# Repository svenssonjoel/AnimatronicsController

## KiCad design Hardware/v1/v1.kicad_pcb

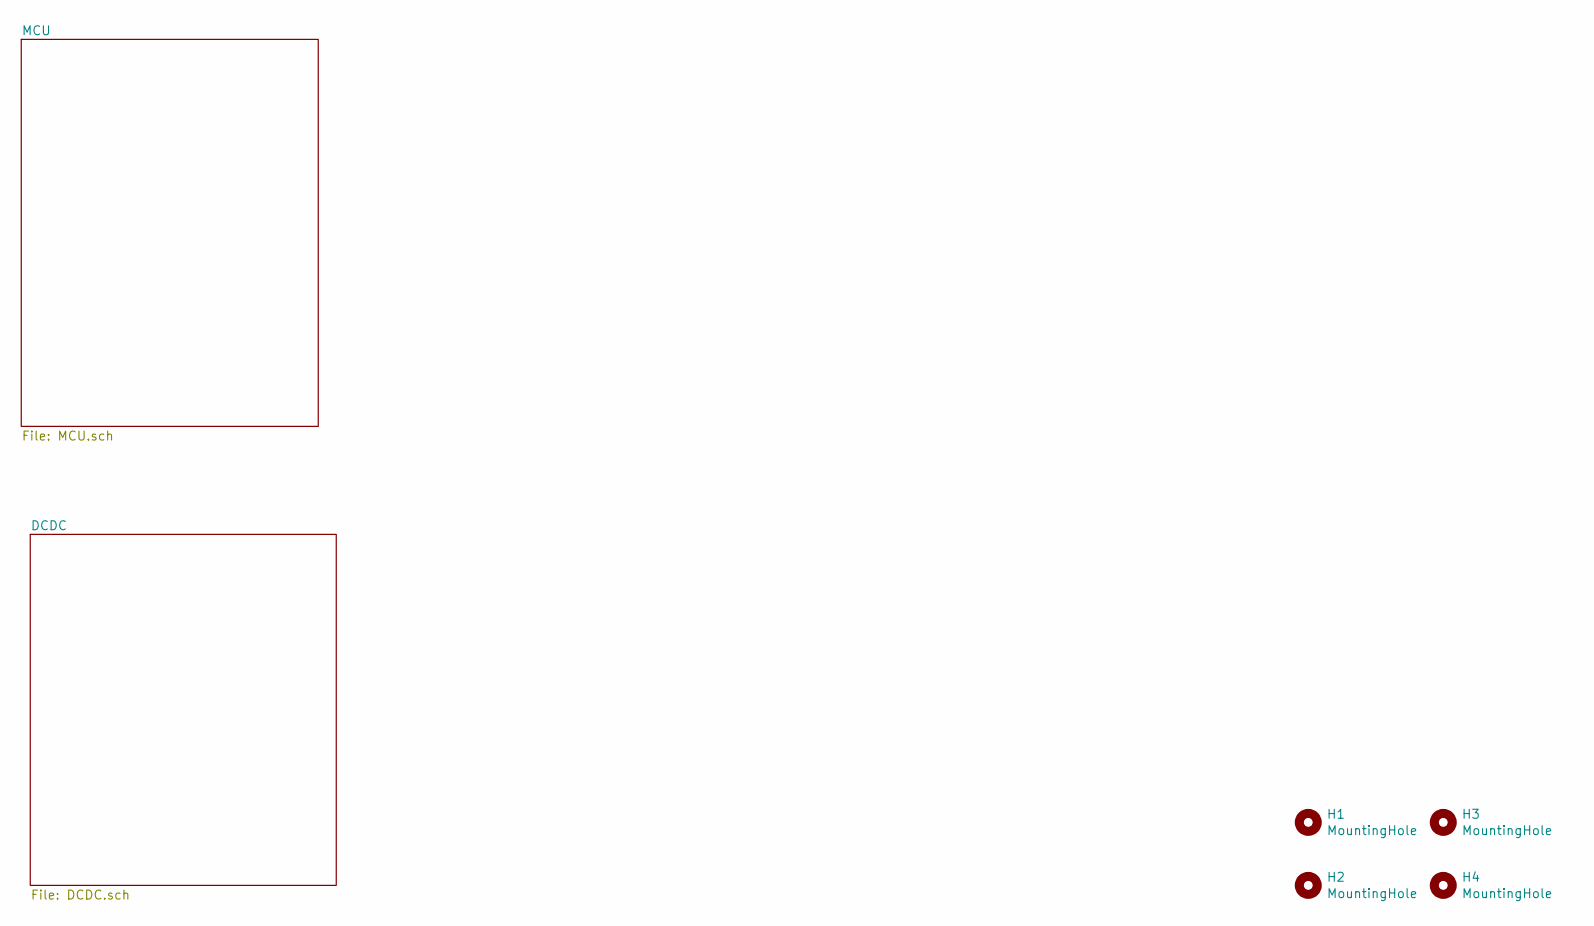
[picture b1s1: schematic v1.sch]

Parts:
H1, H2, H3, H4: MountingHole; MountingHole_3.2mm_M3

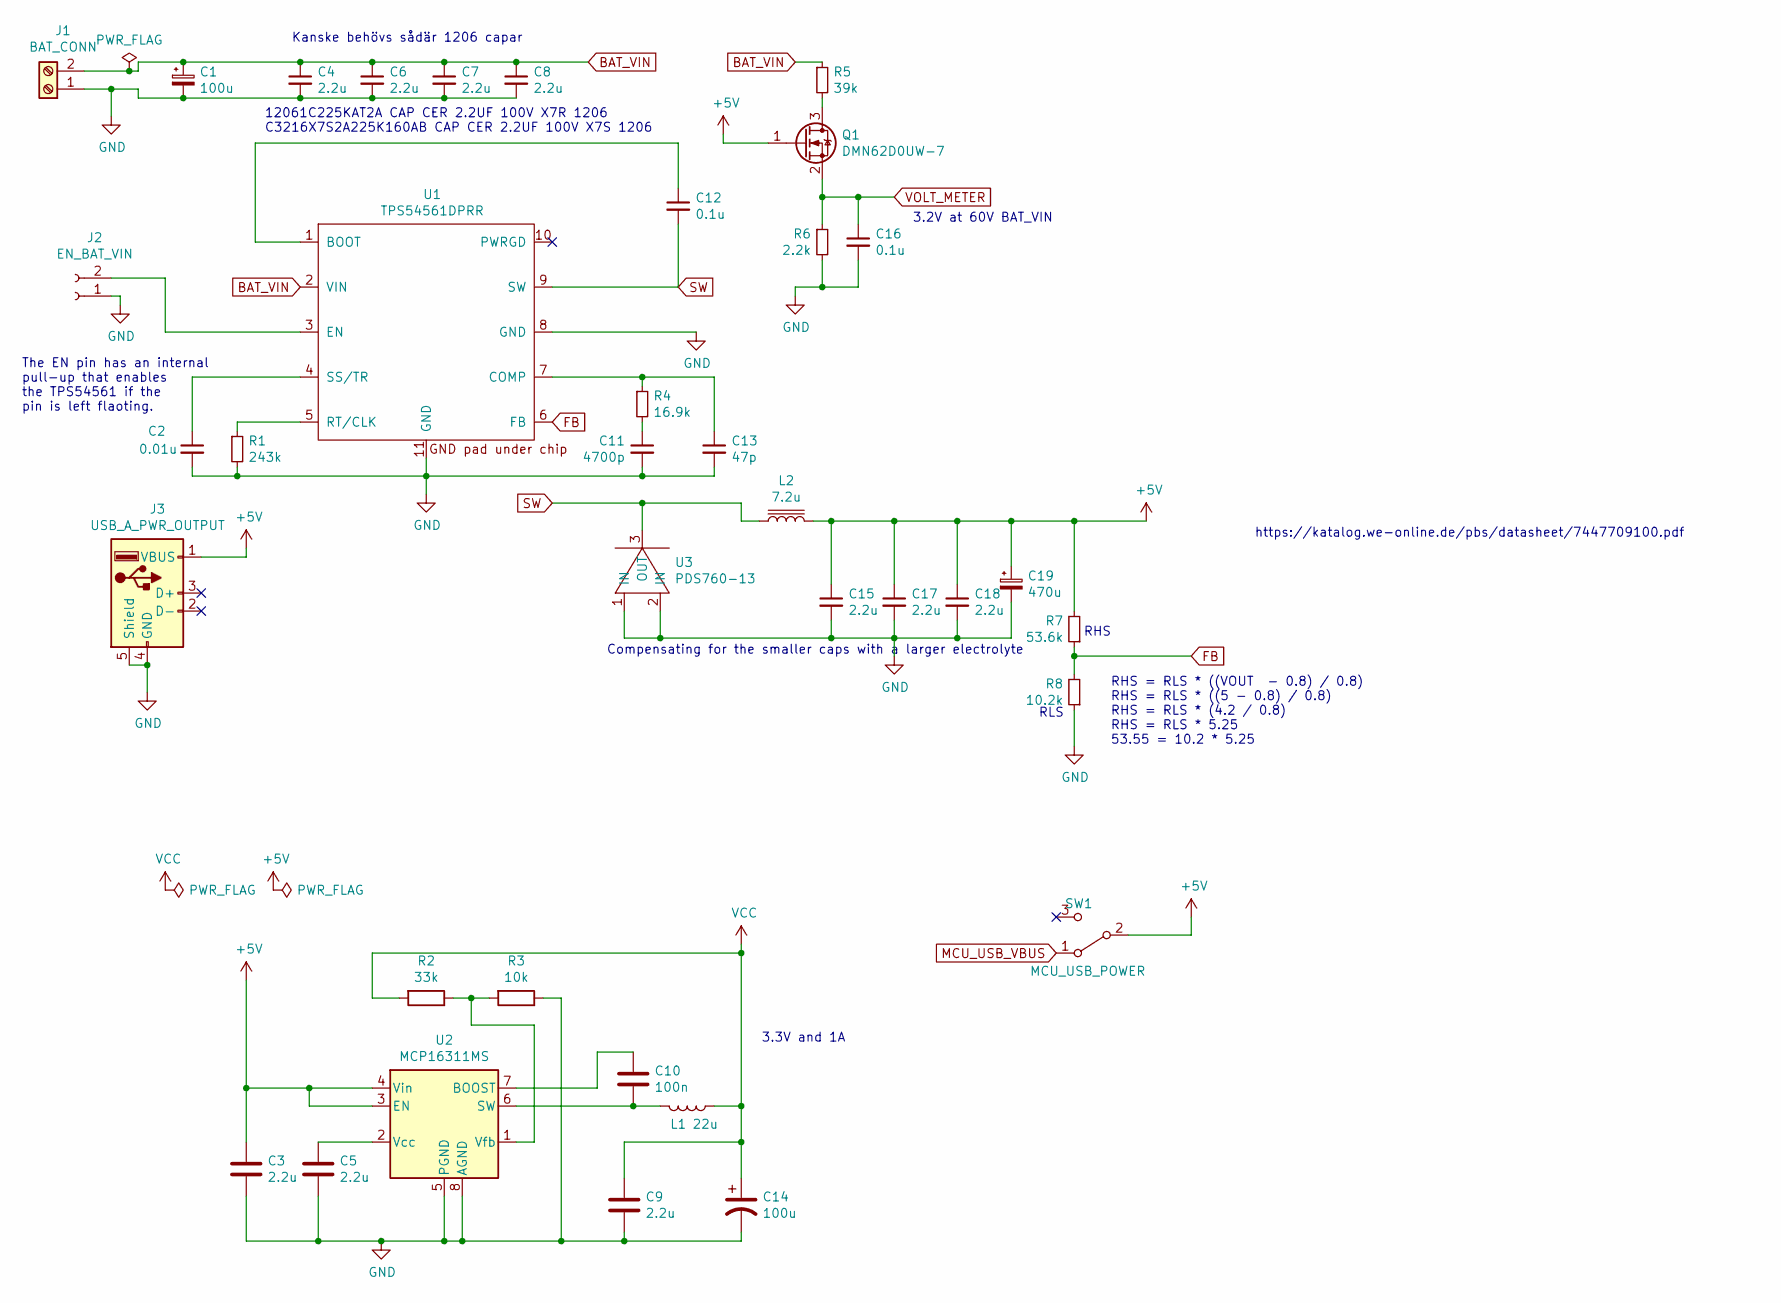
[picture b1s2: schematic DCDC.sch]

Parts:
C1: 100u; CP_Radial_D10.0mm_P5.00mm
C2: 0.01u; C_0603_1608Metric
C3, C5, C9, C15, C17, C18: 2.2u; C_0603_1608Metric
C4, C6, C7, C8: 2.2u; C_1206_3216Metric
C10: 100n; C_0603_1608Metric
C11: 4700p; C_0603_1608Metric
C12, C16: 0.1u; C_0603_1608Metric
C13: 47p; C_0603_1608Metric
C14: 100u; CP_EIA-3528-12_Kemet-T
C19: 470u; CP_Radial_D10.0mm_P5.00mm
J1: BAT_CONN; TerminalBlock_Phoenix_PT-1,5-2-5.0-H_1x02_P5.00mm_Horizontal
J2: EN_BAT_VIN; JST_PH_B2B-PH-K_1x02_P2.00mm_Vertical
J3: USB_A_PWR_OUTPUT; USB_A_Stewart_SS-52100-001_Horizontal
L1: 22u; L_Taiyo-Yuden_MD-5050
L2: 7.2u; L_12x12mm_H8mm
Q1: DMN62D0UW-7; SOT-323_SC-70
R1: 243k; R_0603_1608Metric
R2: 33k; R_0603_1608Metric
R3: 10k; R_0603_1608Metric
R4: 16.9k; R_0603_1608Metric
R5: 39k; R_0603_1608Metric
R6: 2.2k; R_0603_1608Metric
R7: 53.6k; R_0603_1608Metric
R8: 10.2k; R_0603_1608Metric
SW1: MCU_USB_POWER; SW_SPDT_PCM12
U1: TPS54561DPRR; TI-DPR; digikey 296-40803-1-ND
U2: MCP16311MS; MSOP-8_3x3mm_P0.65mm
U3: PDS760-13; POWERDI5

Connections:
+5V: C3.1, C15.1, C17.1, C18.1, C19.1, J3.1 (VBUS), L2.2, Q1.1 (G), R7.2, SW1.2 (B), U2.3 (EN), U2.4 (Vin); also elsewhere on the board
BAT_VIN: C1.1, C4.1, C6.1, C7.1, C8.1, J1.2, R5.1, U1.2 (VIN)
FB: R7.1, R8.2, U1.6 (FB)
GND: C1.2, C2.2, C3.2, C4.2, C5.2, C6.2, C7.2, C8.2, C9.2, C11.2, C13.2, C14.2, C15.2, C16.2, C17.2, C18.2, C19.2, J1.1, J2.1, J3.4 (GND), J3.5 (Shield), R1.2, R3.1, R6.2, R8.1, U1.8 (GND), U1.11 (GND), U2.5 (PGND), U2.8 (AGND), U3.1 (IN), U3.2 (IN); also elsewhere on the board
MCU_USB_VBUS: SW1.1 (A); also elsewhere on the board
unnamed: C2.1, U1.4 (SS/TR)
unnamed: C5.1, U2.2 (Vcc)
unnamed: C10.1, U2.7 (BOOST)
unnamed: C10.2, L1.2, U2.6 (SW)
unnamed: C11.1, R4.2
unnamed: C12.1, U1.1 (BOOT)
unnamed: C13.1, R4.1, U1.7 (COMP)
unnamed: J2.2, U1.3 (EN)
unnamed: Q1.3 (D), R5.2
unnamed: R1.1, U1.5 (RT/CLK)
unnamed: R2.1, R3.2, U2.1 (Vfb)
SW: C12.2, L2.1, U1.9 (SW), U3.3 (OUT)
VCC: C9.1, C14.1, L1.1, R2.2; also elsewhere on the board
VOLT_METER: C16.1, Q1.2 (S), R6.1; also elsewhere on the board

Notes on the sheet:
3.3V and 1A
The EN pin has an internal pull-up that enables the TPS54561 if the pin is left flaoting.
Kanske behövs sådär 1206 capar
https://katalog.we-online.de/pbs/datasheet/7447709100.pdf
3.2V at 60V BAT_VIN
12061C225KAT2A CAP CER 2.2UF 100V X7R 1206 C3216X7S2A225K160AB CAP CER 2.2UF 100V X7S 1206
RHS = RLS * ((VOUT - 0.8) / 0.8) RHS = RLS * ((5 - 0.8) / 0.8) RHS = RLS * (4.2 / 0.8) RHS = RLS * 5.25 53.55 = 10.2 * 5.25
RHS
RLS
Compensating for the smaller caps with a larger electrolyte

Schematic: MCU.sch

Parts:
C20, C23: 15p; C_0603_1608Metric
C21, C22, C24, C25, C27, C28, C29, C30, C31, C32, C33, C34: 2.2u; C_0603_1608Metric
C26: 100n; C_0603_1608Metric
D1: RED; LED_0603_1608Metric
D2: GREEN; LED_0603_1608Metric
J4: GPIO1; JST_PH_B4B-PH-K_1x04_P2.00mm_Vertical
J5: GPIO2; JST_PH_B4B-PH-K_1x04_P2.00mm_Vertical
J6: GPIO3; JST_PH_B4B-PH-K_1x04_P2.00mm_Vertical
J10: DACS; JST_PH_B2B-PH-K_1x02_P2.00mm_Vertical
J11: SERV_0; PinHeader_1x03_P2.54mm_Vertical
J12: SERV_1; PinHeader_1x03_P2.54mm_Vertical
J13: SERV_2; PinHeader_1x03_P2.54mm_Vertical
J14: SERV_3; PinHeader_1x03_P2.54mm_Vertical
J15: SERV_4; PinHeader_1x03_P2.54mm_Vertical
J16: SERV_5; PinHeader_1x03_P2.54mm_Vertical
J17: SERV_6; PinHeader_1x03_P2.54mm_Vertical
J18: SERV_7; PinHeader_1x03_P2.54mm_Vertical
J19: CAN; JST_PH_B4B-PH-K_1x04_P2.00mm_Vertical
J20: USB_B_Mini; USB_Mini-B_Lumberg_2486_01_Horizontal
P1: SWD; JST_PH_B6B-PH-K_1x06_P2.00mm_Vertical
R9, R10, R22, R27: 1k; R_0603_1608Metric
R11, R14, R15, R16, R17, R18, R19, R20, R21: 220R; R_0603_1608Metric
R12, R13: 22R; R_0603_1608Metric
SW2: BOOT0; SW_SPDT_PCM12
U4: BMI160; Bosch_LGA-14_3x2.5mm_P0.5mm; digikey 828-1057-1-ND
U5: STM32F405RGTx; LQFP-64_10x10mm_P0.5mm
U6: TJA1051TK-3; DFN-8-1EP_3x3mm_P0.65mm_EP1.55x2.4mm
Y1: 8Mhz; Crystal_SMD_5032-4Pin_5.0x3.2mm

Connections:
+5V: C28.2, J11.2, J12.2, J13.2, J14.2, J15.2, J16.2, J17.2, J18.2, J19.4, U6.3 (VCC); also elsewhere on the board
/MCU/GP1: J4.2, U5.9 (PC1)
/MCU/GP2: J4.3, U5.10 (PC2)
/MCU/GP3: J4.4, U5.11 (PC3)
/MCU/GP4: J5.2, U5.53 (PC12)
/MCU/GP5: J5.3, U5.2 (PC13)
/MCU/GP6: J5.4, U5.3 (PC14)
/MCU/GP7: J6.2, U5.22 (PA6)
/MCU/GP8: J6.3, U5.23 (PA7)
/MCU/GP9: J6.4, U5.41 (PA8)
/MCU/SERV1: R14.2, U5.14 (PA0)
/MCU/SERV2: R15.2, U5.15 (PA1)
/MCU/SERV3: R16.2, U5.16 (PA2)
/MCU/SERV4: R17.2, U5.17 (PA3)
/MCU/SERV5: R18.2, U5.26 (PB0)
/MCU/SERV6: R19.2, U5.27 (PB1)
/MCU/SERV7: R20.2, U5.55 (PB3)
/MCU/SERV8: R21.2, U5.56 (PB4)
CANH: J19.3, R11.1, U6.7 (CANH)
CANL: J19.2, R11.2, U6.6 (CANL)
CAN_RX: U5.61 (PB8), U6.4 (RXD)
CAN_TX: U5.62 (PB9), U6.1 (TXD)
GND: C20.1, C21.2, C22.2, C23.1, C24.2, C25.2, C26.1, C27.2, C28.1, C29.2, C30.2, C31.2, C32.2, C33.2, C34.2, D1.1 (K), D2.1 (K), J4.1, J5.1, J6.1, J11.3, J12.3, J13.3, J14.3, J15.3, J16.3, J17.3, J18.3, J19.1, J20.5, J20.6, P1.4, SW2.1 (A), U4.1 (SDO), U4.6 (GNDIO), U4.7 (GND), U5.12 (VSSA), U5.18 (VSS), U5.28 (PB2), U5.63 (VSS), U6.2 (GND), U6.8 (S), U6.9 (GND), Y1.2, Y1.4; also elsewhere on the board
IMU_INT2: U4.9 (INT2), U5.25 (PC5)
LED0: R22.2, U5.51 (PC10)
LED1: R27.2, U5.52 (PC11)
MCU_USB_DM: J20.2, R12.1
MCU_USB_DP: J20.3, R13.1
MCU_USB_VBUS: J20.1, U5.42 (PA9); also elsewhere on the board
NRST: C26.2, P1.2, U5.7 (NRST)
unnamed: C20.2, U5.6 (PH1), Y1.3
unnamed: C23.2, U5.5 (PH0), Y1.1
unnamed: C24.1, U5.31 (VCAP_1)
unnamed: C25.1, U5.47 (VCAP_2)
unnamed: D1.2 (A), R22.1
unnamed: D2.2 (A), R27.1
unnamed: J10.1, U5.20 (PA4)
unnamed: J10.2, U5.21 (PA5)
unnamed: J11.1, R14.1
unnamed: J12.1, R15.1
unnamed: J13.1, R16.1
unnamed: J14.1, R17.1
unnamed: J15.1, R18.1
unnamed: J16.1, R19.1
unnamed: J17.1, R20.1
unnamed: J18.1, R21.1
unnamed: R12.2, U5.44 (PA11)
unnamed: R13.2, U5.45 (PA12)
unnamed: SW2.2 (B), U5.60 (BOOT0)
SCL: R10.2, U4.13 (SCx), U5.29 (PB10)
SDA: R9.2, U4.14 (SDx), U5.30 (PB11)
SWCLK: P1.5, U5.49 (PA14)
SWDIO: P1.3, U5.46 (PA13)
VCC: C21.1, C22.1, C27.1, C29.1, C30.1, C31.1, C32.1, C33.1, C34.1, P1.6, R9.1, R10.1, SW2.3 (C), U4.5 (VDDIO), U4.8 (VDD), U4.12 (CSB), U5.1 (VBAT), U5.13 (VDDA), U5.19 (VDD), U5.32 (VDD), U5.48 (VDD), U5.64 (VDD), U6.5 (VIO); also elsewhere on the board
VOLT_METER: U5.8 (PC0); also elsewhere on the board

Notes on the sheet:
place close to pin 1, 19, 32, 48, 64, 13
PC0 - PC5 has ADC
Servo connectors
LQFP64 TIM 2,3,4,5 PWM (TIM1 is more capable than TIM2 - 5 TIM1 CH1 PIN 23 (N), 27(N), 34(N), 36(N), 41 TIM1 CH2 PIN 42 TIM1 CH3 PIN 43 TIM1 CH4 PIN 44 (Maybe prefer these ?) TIM2 CH1 PIN 14, 21 TIM2 CH2 PIN 15, 55 TIM2 CH3 PIN 16, 29 TIM2 CH4 PIN 17, 30 TIM3 CH1 PIN 37, 56 TIM3 CH2 PIN 38 TIM3 CH3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
Dubbelkoll CSB - VCC. vi ska ha I2c
Place near VDD/GND BMI160

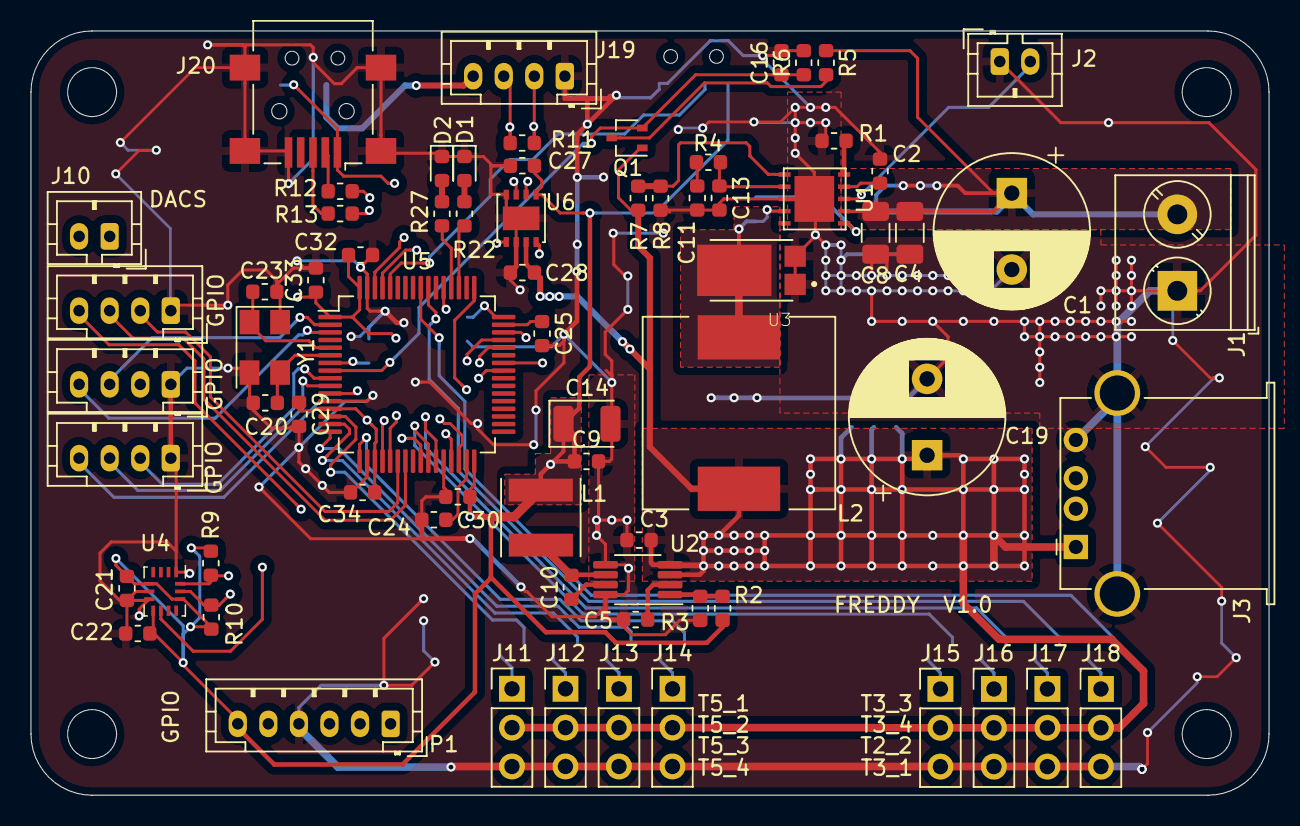
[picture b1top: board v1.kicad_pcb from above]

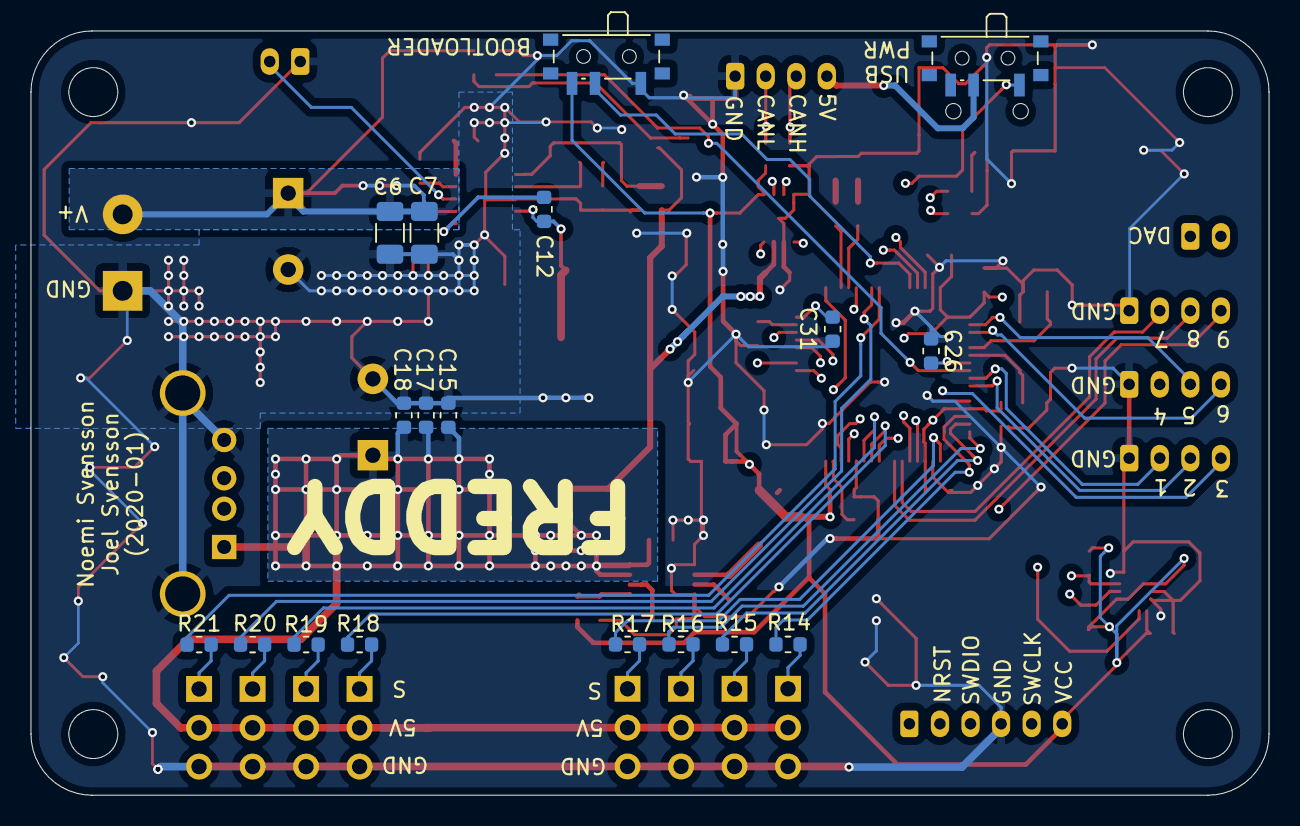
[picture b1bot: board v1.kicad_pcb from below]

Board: 4 copper layers, 81.0 x 50.0 mm, 93 parts (18 on the bottom side), 69 nets.

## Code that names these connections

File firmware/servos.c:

/*
    Copyright 2020 Joel Svensson	svenssonjoel@yahoo.se

    This program is free software: you can redistribute it and/or modify
    it under the terms of the GNU General Public License as published by
    the Free Software Foundation, either version 3 of the License, or
    (at your option) any later version.

    This program is distributed in the hope that it will be useful,
    but WITHOUT ANY WARRANTY; without even the implied warranty of
    MERCHANTABILITY or FITNESS FOR A PARTICULAR PURPOSE.  See the
    GNU General Public License for more details.

    You should have received a copy of the GNU General Public License
    along with this program.  If not, see <http://www.gnu.org/licenses/>.
*/

#include <stdint.h>
#include "servos.h"

#include "hal.h"
#include "hal_pwm.h"
#include "hal_pal.h"

/* 
   Alternate function mappings for 
   PA0 - PA3 to use tim 5 
   PB0 - PB1 to use tim 3
   PB3       to use tim 2
    ---- PB4       to use tim 3 --- should not have used this!
*/ 
#define GPIO_AF_TIM5   ((uint8_t)0x02)
#define GPIO_AF_TIM3   ((uint8_t)0x02)  
#define GPIO_AF_TIM2   ((uint8_t)0x01)

/* pwmconfig to use for TIM5.
   Here all channels are used. 
*/ 
static PWMConfig pwmcfg_tim5 = {
  1000000,
  20000,
  NULL,
  {
    {PWM_OUTPUT_ACTIVE_HIGH, NULL},
    {PWM_OUTPUT_ACTIVE_HIGH, NULL},
    {PWM_OUTPUT_ACTIVE_HIGH, NULL},
    {PWM_OUTPUT_ACTIVE_HIGH, NULL}
  },
  0,
  0
};

static PWMConfig pwmcfg_tim3 = {
  1000000,
  20000,
  NULL,
  {
    {PWM_OUTPUT_ACTIVE_HIGH, NULL},
    {PWM_OUTPUT_DISABLED,    NULL},
    {PWM_OUTPUT_ACTIVE_HIGH, NULL},
    {PWM_OUTPUT_ACTIVE_HIGH, NULL}
  },
  0,
  0,
};

/*
static PWMConfig pwmcfg_tim2 = {
  1000000,
  20000,
  NULL,
  {
    {PWM_OUTPUT_DISABLED,    NULL},
    {PWM_OUTPUT_ACTIVE_HIGH, NULL},
    {PWM_OUTPUT_DISABLED,    NULL},
    {PWM_OUTPUT_DISABLED,    NULL},
  },
  0,
  0,
};
*/

void servos_init(void) {

  palSetPadMode(GPIOA, 0,
		PAL_MODE_ALTERNATE(GPIO_AF_TIM5) |
		PAL_STM32_OSPEED_HIGHEST |
		PAL_STM32_PUPDR_FLOATING);
  palSetPadMode(GPIOA, 1,
		PAL_MODE_ALTERNATE(GPIO_AF_TIM5) |
		PAL_STM32_OSPEED_HIGHEST |
		PAL_STM32_PUPDR_FLOATING);
  palSetPadMode(GPIOA, 2,
		PAL_MODE_ALTERNATE(GPIO_AF_TIM5) |
		PAL_STM32_OSPEED_HIGHEST |
		PAL_STM32_PUPDR_FLOATING);
  palSetPadMode(GPIOA, 3,
		PAL_MODE_ALTERNATE(GPIO_AF_TIM5) |
		PAL_STM32_OSPEED_HIGHEST |
		PAL_STM32_PUPDR_FLOATING);

  palSetPadMode(GPIOB, 0,
		PAL_MODE_ALTERNATE(GPIO_AF_TIM3) |
	        PAL_STM32_OSPEED_HIGHEST |
		PAL_STM32_PUPDR_FLOATING);
  palSetPadMode(GPIOB, 1,
		PAL_MODE_ALTERNATE(GPIO_AF_TIM3) |
		PAL_STM32_OSPEED_HIGHEST |
		PAL_STM32_PUPDR_FLOATING);
  palSetPadMode(GPIOB, 4,
		PAL_MODE_ALTERNATE(GPIO_AF_TIM3) |
		PAL_STM32_OSPEED_HIGHEST |
		PAL_STM32_PUPDR_FLOATING);

  //palSetPadMode(GPIOB, 3,
  //		PAL_MODE_ALTERNATE(GPIO_AF_TIM2) |
  //		PAL_STM32_OSPEED_HIGHEST |
  //		PAL_STM32_PUPDR_FLOATING);

  
  //pwmStart(&PWMD2, &pwmcfg_tim2);
  pwmStart(&PWMD3, &pwmcfg_tim3);
  pwmStart(&PWMD5, &pwmcfg_tim5);

  //pwmEnableChannel(&PWMD2, 1, 0); /* Second channel of tim 2 */

  pwmEnableChannel(&PWMD5, 0, 0);
  pwmEnableChannel(&PWMD5, 1, 0);
  pwmEnableChannel(&PWMD5, 2, 0);
  pwmEnableChannel(&PWMD5, 3, 0);
  
  pwmEnableChannel(&PWMD3, 0, 0);
  pwmEnableChannel(&PWMD3, 2, 0);
  pwmEnableChannel(&PWMD3, 3, 0);
}
  

extern void servos_set_duty(uint8_t servos, unsigned int duty) {

  if (servos & SERVO1) {
    pwmEnableChannel(&PWMD5, 0, PWM_PERCENTAGE_TO_WIDTH(&PWMD5, duty));
  }

  if (servos & SERVO2) {
    pwmEnableChannel(&PWMD5, 1, PWM_PERCENTAGE_TO_WIDTH(&PWMD5, duty));
  }

  if (servos & SERVO3) {
    pwmEnableChannel(&PWMD5, 2, PWM_PERCENTAGE_TO_WIDTH(&PWMD5, duty));
  }

  if (servos & SERVO4) {
    pwmEnableChannel(&PWMD5, 3, PWM_PERCENTAGE_TO_WIDTH(&PWMD5, duty));
  }

  if (servos & SERVO5) { 
    pwmEnableChannel(&PWMD3, 0, PWM_PERCENTAGE_TO_WIDTH(&PWMD3, duty));
  }

  if (servos & SERVO6) {
    pwmEnableChannel(&PWMD3, 2, PWM_PERCENTAGE_TO_WIDTH(&PWMD3, duty));
  }

  if (servos & SERVO7) {
    //pwmEnableChannel(&PWMD2, 1, PWM_PERCENTAGE_TO_WIDTH(&PWMD2, duty)); 
  }

  if (servos & SERVO8) {
    pwmEnableChannel(&PWMD3, 3, PWM_PERCENTAGE_TO_WIDTH(&PWMD3, duty));
  }

}

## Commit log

2020-01-01 schematics done
2020-01-02 saving
2020-01-03 ANITRONBO V1_0
2020-01-04 doneish
2020-01-09 tweaks and simplification
2020-01-09 adding some descriptions on F silks
2020-01-09 GERBER
2020-01-16 added some text to silks
2020-02-10 started on firmware
2020-02-10 added firmware
